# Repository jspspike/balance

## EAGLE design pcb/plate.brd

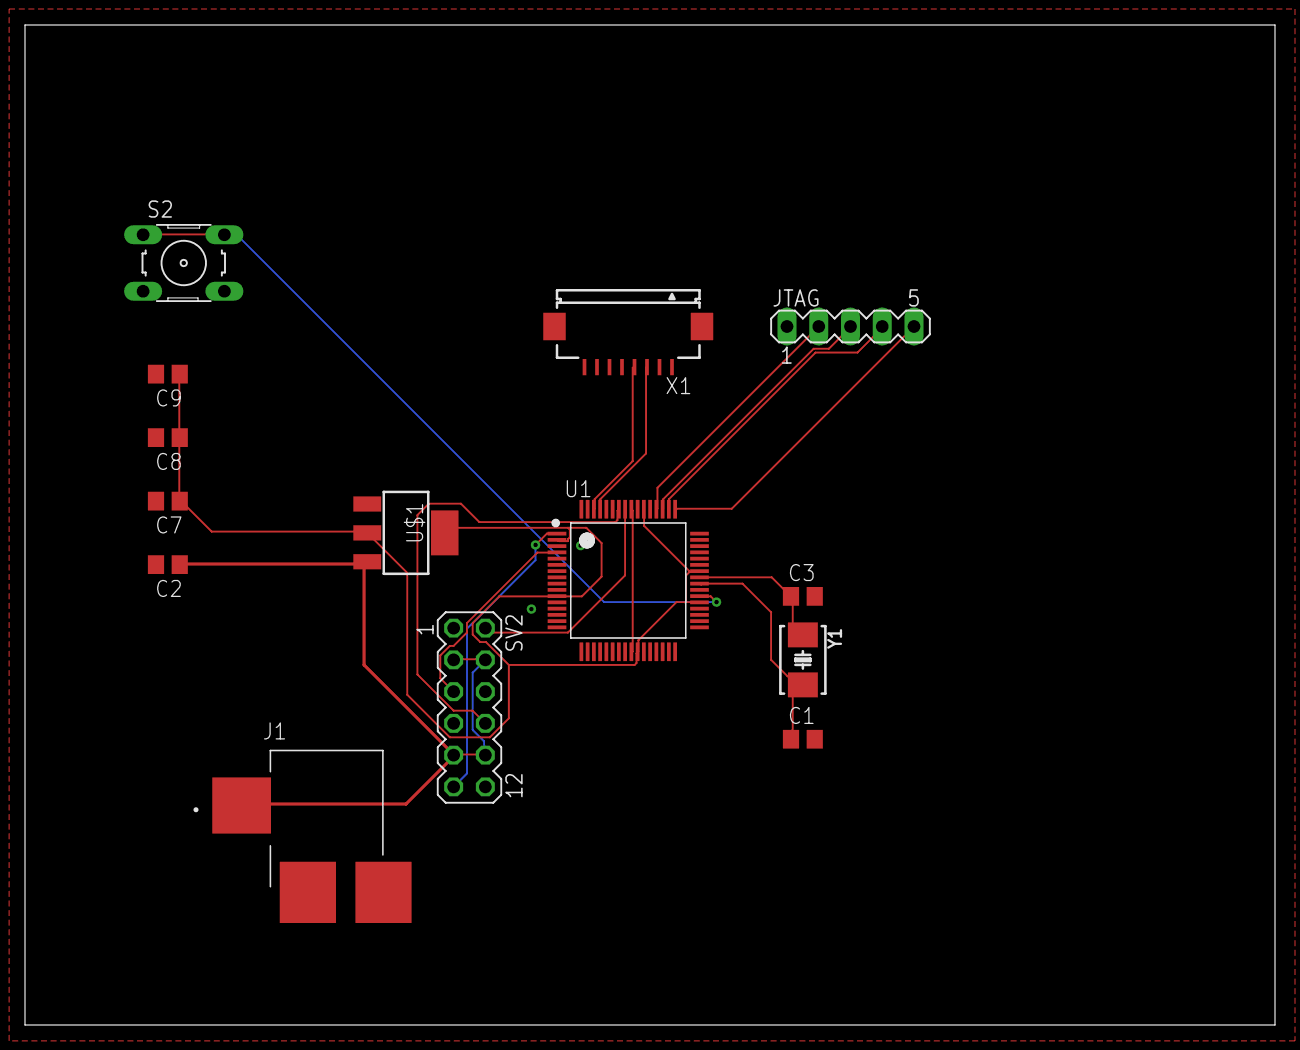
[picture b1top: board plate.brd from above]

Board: 2 copper layers, 100.0 x 80.0 mm, 14 parts (0 on the bottom side), 17 nets.

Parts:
C1, C3, C8, C9: 1uF; C0805
C2, C7: 4.7uF; C0805
J1: PJ-070BH-SMT-TR; CUI_PJ-PJ-070BH-SMT-TR
JTAG: MA05-1
S2: B3F-10XX
SV2: MA06-2
U1: TM4C123GH6PMI; QFP50P1200X1200X160-64N
U$1: AP2114H-3.3TRG1; SOT223
X1: FH12-08S-1SH
Y1: NX5032GA; 2-SMD-5X3

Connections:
3.3V: C7.1, C8.1, C9.1, U1.2, U1.11, U1.26, U1.37, U1.42, U1.54, U$1.2, U$1.4
5V: C2.1, J1.1, SV2.3, SV2.4, SV2.9, SV2.10, U$1.3
GND: C1.2, C2.2, C3.2, C7.2, C8.2, C9.2, J1.2, JTAG.1, S2.3, S2.4, SV2.1, SV2.6, SV2.7, SV2.12, U1.3, U1.12, U1.27, U1.34, U1.35, U1.39, U1.55, U$1.1, X1.2
unnamed: S2.1, S2.2, U1.38
OSC0: C1.1, U1.40, Y1.2
OSC1: C3.1, U1.41, Y1.1
RESX: U1.61, X1.3
RESY: U1.62, X1.4
SERV0: SV2.8, U1.58
SERV1: SV2.2, U1.57
SERV2: SV2.11, U1.1
SERV3: SV2.5, U1.4
TCK: JTAG.2, U1.52
TDI: JTAG.4, U1.50
TDO: JTAG.5, U1.49
TMS: JTAG.3, U1.51
VDDC: U1.25, U1.56

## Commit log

2019-10-25 AP2114
2019-10-25 Made lib folder
2019-10-25 Added schematic
2019-10-25 Added pcb
2019-10-25 remove prolog
2019-10-29 Redo schematic in kicad
    Components are placed but not routed yet
2019-10-31 Modify component placement and fix transistor circuits
2019-10-31 Route the board
2019-11-01 Add mounting holes and remove some vias
2019-11-02 test
2019-11-02 finished report
2019-11-02 added names to report
2019-11-02 added BOM
2019-11-24 Add test code for servos
2019-11-25 Fix PWM bugs
    Manual servo control works
2019-12-04 Added screen interface
2019-12-04 added adc to main
2019-12-04 adc_init complete
2019-12-04 Added pid
2019-12-04 change to software trigger
2019-12-05 Added more pid
2019-12-05 Added buffer
2019-12-05 Add screen breakout
2019-12-10 Rewrite code
2019-12-11 Get LEDs and speaker working on actual board
2019-12-17 Add setpoints and mess with velocity control
2019-12-17 Add more setpoints and start on motion profiles
2019-12-17 Small tweaks for submission
